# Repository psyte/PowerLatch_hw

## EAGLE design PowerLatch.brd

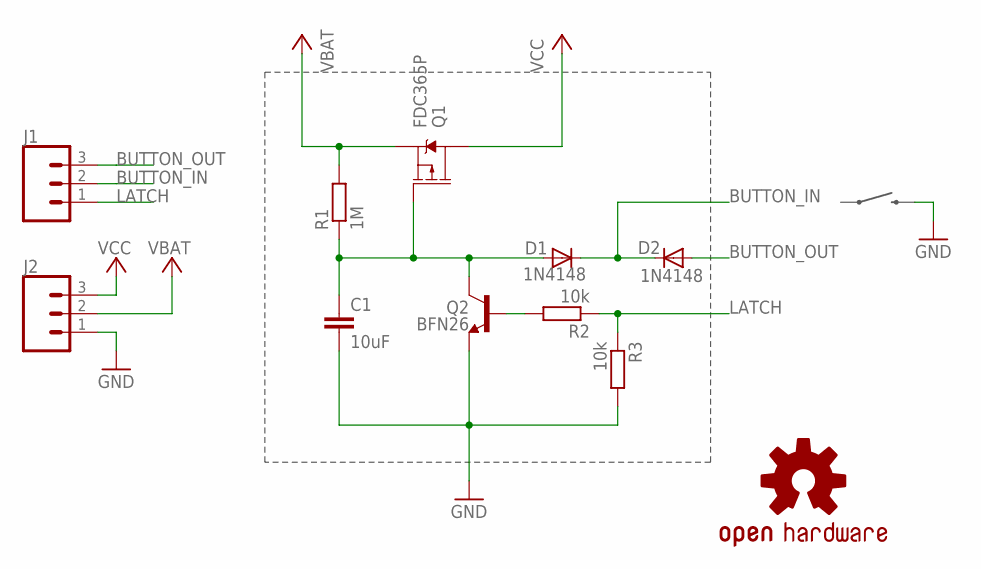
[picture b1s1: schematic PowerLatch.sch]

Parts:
C1: 10uF; C0603
D1, D2: 1N4148; SOD523
J1, J2: 455-1750-1-ND; 1X03
LOGO1: OSHW-LOGOS; OSHW-LOGO-S
Q1: FDC365P; SSOT6
Q2: BFN26; SOT23-3
R1: 1M; R0603
R2, R3: 10k; R0603

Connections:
BUTTON_IN: D1.C, D2.C, J1.2
BUTTON_OUT: D2.A, J1.3
GND: C1.2, J2.1, Q2.2 (E), R3.2
LATCH: J1.1, R2.1, R3.1
unnamed: Q2.1 (B), R2.2
unnamed: C1.1, D1.A, Q1.3 (G), Q2.3 (C), R1.1
VBAT: J2.2, Q1.4 (S), R1.2
VCC: J2.3, Q1.1 (D), Q1.2 (D), Q1.5 (D), Q1.6 (D)

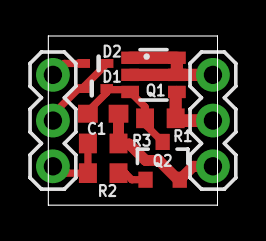
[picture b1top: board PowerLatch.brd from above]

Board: 2 copper layers, 9.4 x 9.4 mm, 11 parts (1 on the bottom side), 8 nets.

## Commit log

2019-05-08 Rev. 1.0

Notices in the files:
parts and their libraries:
SparkFun-Connectors: Licensing: Creative Commons ShareAlike 4.0 International - https://creativecommons.org/licenses/by-sa/4.0
